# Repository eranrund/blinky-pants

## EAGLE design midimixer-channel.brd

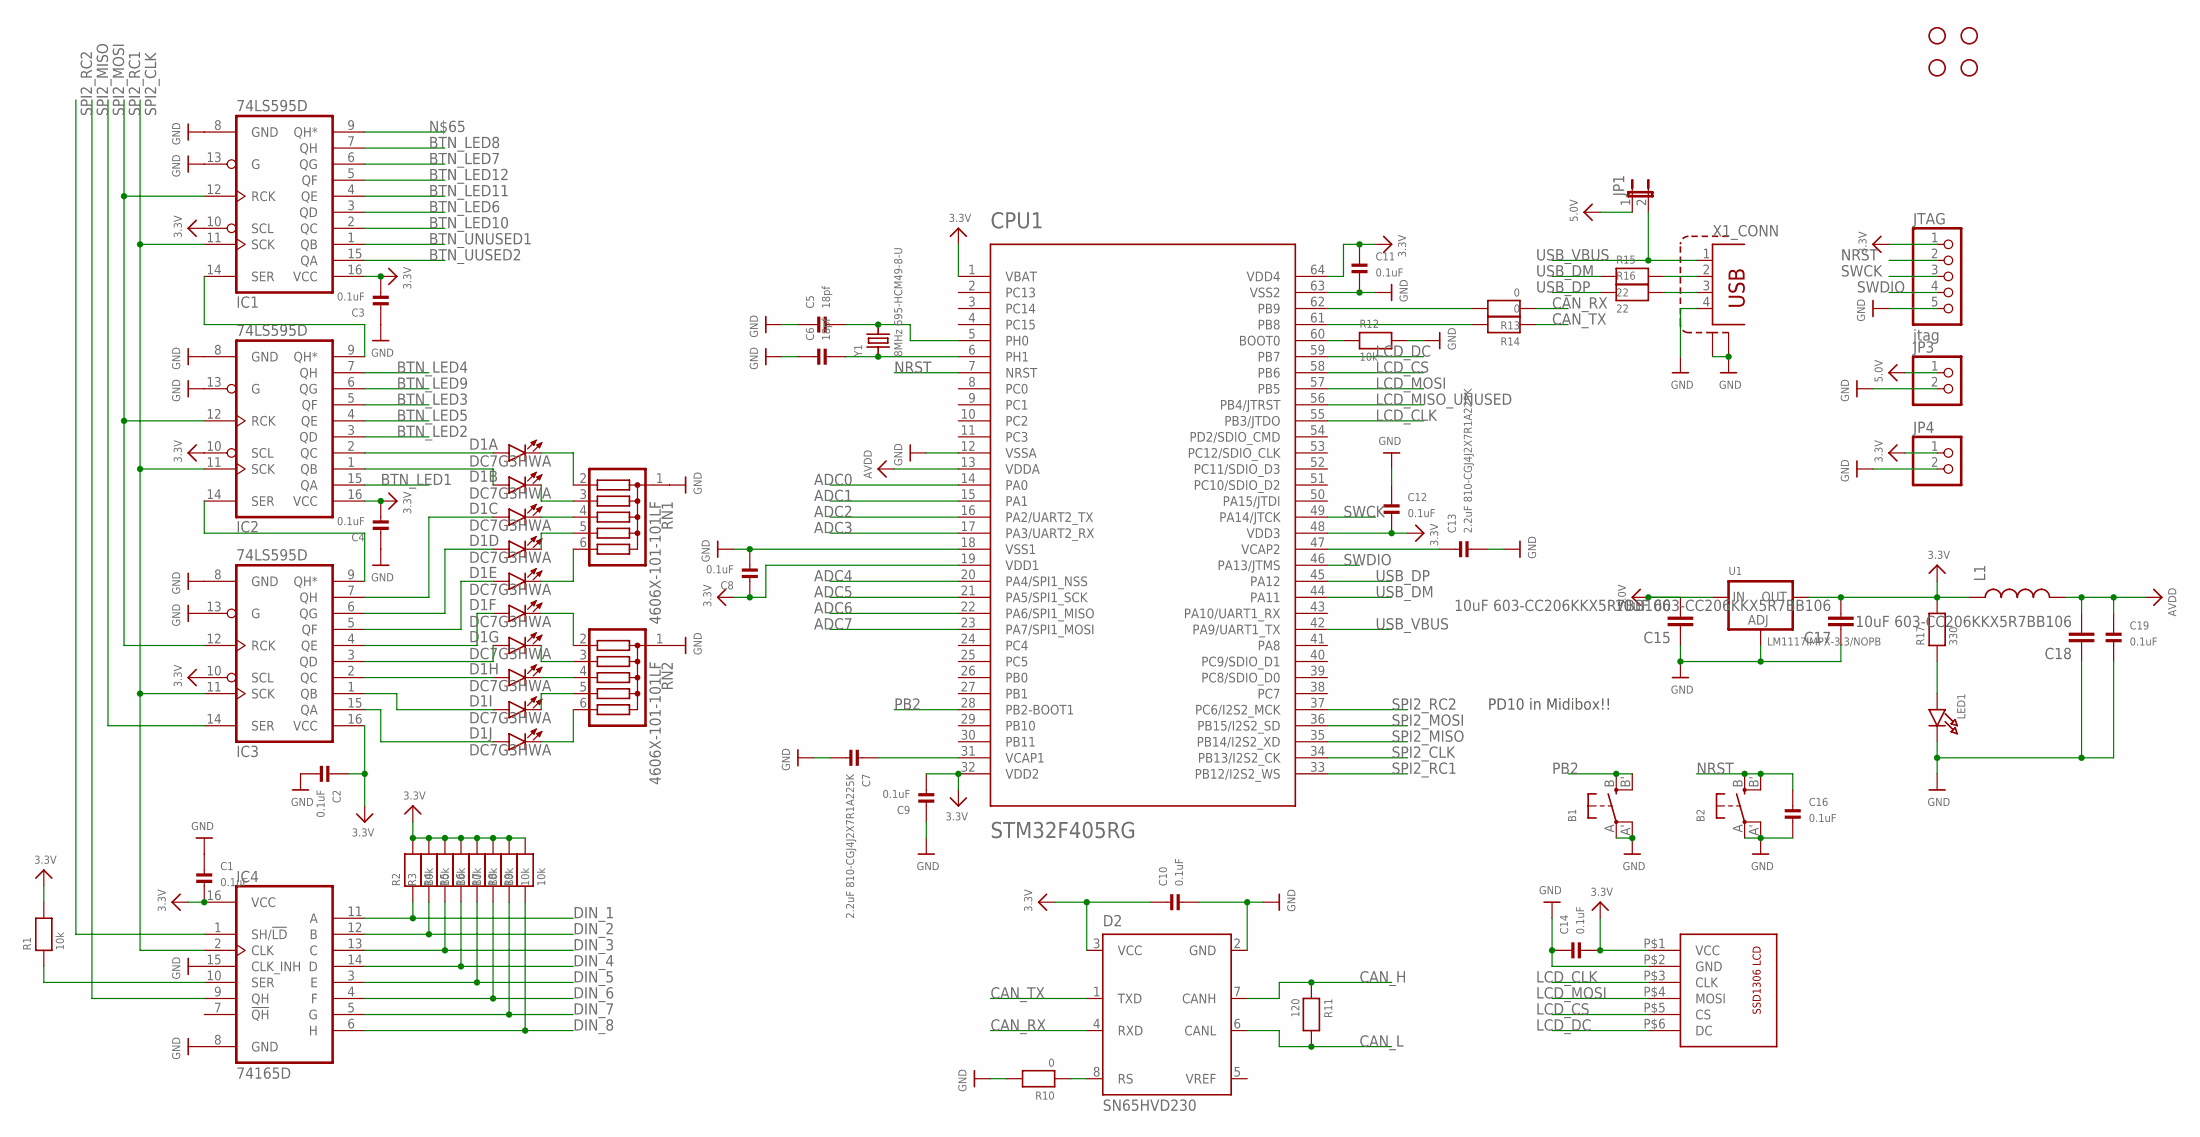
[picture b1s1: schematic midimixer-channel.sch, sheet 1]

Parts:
B1, B2: SWITCH_TACT_SMT; EVQ-Q2
C1, C2, C3, C4, C8, C9, C10, C11, C12, C14, C16, C19: 0.1uF; 0603
C5, C6: 18pf; 0603
C7, C13: 2.2uF 810-CGJ4J2X7R1A225K; 0805
C15, C17, C18: 10uF 603-CC206KKX5R7BB106; 1206
CPU1: STM32F405RG; TQFP64
D1: DC7G3HWA; LED_BARGAPH_10
D2: SN65HVD230; SO8
H1, H2, H3, H4: STAND-OFF
IC1, IC2, IC3: 74LS595D; SO16
IC4: 74165D; SO16
JP1: JUMPER2
JP3, JP4: HEADER-1X2ROUND; 1X02_ROUND
JTAG: jtag; 1X05_ROUND_76
L1: INDUCTOR0805; 0805
LCD1: SSD1306-ALI
LED1: LED0603; CHIPLED_0603
R1, R2, R3, R4, R5, R6, R7, R8, R9, R12: 10k; _0603
R10, R13, R14: 0; _0603
R11: 120; _0603
R15, R16: 22; 0603
R17: 330; 0603
RN1, RN2: 4606X-101-101LF; SIL6
U1: LM1117IMPX-3.3/NOPB; SOT223-R
X1: TE-292304-1
Y1: 8MHz 695-HCM49-8-U; HC49UP

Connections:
3.3V: C1.2, C2.1, C3.2, C4.2, C8.1, C9.2, C10.1, C11.1, C12.2, C14.2, C17.2, CPU1.1 (VBAT), CPU1.19 (VDD1), CPU1.32 (VDD2), CPU1.48 (VDD3), CPU1.64 (VDD4), D2.3 (VCC), IC1.10 (SCL), IC1.16 (VCC), IC2.10 (SCL), IC2.16 (VCC), IC3.10 (SCL), IC3.16 (VCC), IC4.16 (VCC), JP4.1, JTAG.1, L1.1, LCD1.P$1 (VCC), R1.2, R2.2, R3.2, R4.2, R5.2, R6.2, R7.2, R8.2, R9.2, R17.2, U1.2 (OUT); also elsewhere on the board
5.0V: C15.2, JP1.1, JP3.1, U1.3 (IN)
ADC0: CPU1.14 (PA0); also elsewhere on the board
ADC1: CPU1.15 (PA1); also elsewhere on the board
ADC2: CPU1.16 (PA2/UART2_TX); also elsewhere on the board
ADC3: CPU1.17 (PA3/UART2_RX); also elsewhere on the board
ADC4: CPU1.20 (PA4/SPI1_NSS); also elsewhere on the board
ADC5: CPU1.21 (PA5/SPI1_SCK); also elsewhere on the board
ADC6: CPU1.22 (PA6/SPI1_MISO); also elsewhere on the board
ADC7: CPU1.23 (PA7/SPI1_MOSI); also elsewhere on the board
AVDD: C18.2, C19.1, CPU1.13 (VDDA), L1.2
BTN_LED1: IC2.15 (QA); also elsewhere on the board
BTN_LED2: IC2.3 (QD); also elsewhere on the board
BTN_LED3: IC2.5 (QF); also elsewhere on the board
BTN_LED4: IC2.7 (QH); also elsewhere on the board
BTN_LED5: IC2.4 (QE); also elsewhere on the board
BTN_LED6: IC1.3 (QD); also elsewhere on the board
BTN_LED7: IC1.6 (QG); also elsewhere on the board
BTN_LED8: IC1.7 (QH); also elsewhere on the board
BTN_LED9: IC2.6 (QG); also elsewhere on the board
BTN_LED10: IC1.2 (QC); also elsewhere on the board
BTN_LED11: IC1.4 (QE); also elsewhere on the board
BTN_LED12: IC1.5 (QF); also elsewhere on the board
BTN_UNUSED1: IC1.1 (QB)
BTN_UUSED2: IC1.15 (QA)
CAN_H: D2.7 (CANH), R11.1
CAN_L: D2.6 (CANL), R11.2
CAN_RX: D2.4 (RXD), R13.1
CAN_TX: D2.1 (TXD), R14.1
DIN_1: IC4.11 (A), R2.1; also elsewhere on the board
DIN_2: IC4.12 (B), R3.1; also elsewhere on the board
DIN_3: IC4.13 (C), R4.1; also elsewhere on the board
DIN_4: IC4.14 (D), R5.1
DIN_5: IC4.3 (E), R6.1; also elsewhere on the board
DIN_6: IC4.4 (F), R7.1; also elsewhere on the board
DIN_7: IC4.5 (G), R8.1; also elsewhere on the board
DIN_8: IC4.6 (H), R9.1
GND: B1.A, B1.A' (P1), B2.A, B2.A' (P1), C1.1, C2.2, C3.1, C4.1, C5.1, C6.1, C7.2, C8.2, C9.1, C10.2, C11.2, C12.1, C13.2, C14.1, C15.1, C16.2, C17.1, C18.1, C19.2, CPU1.12 (VSSA), CPU1.18 (VSS1), CPU1.63 (VSS2), D2.2 (GND), IC1.8 (GND), IC1.13 (G), IC2.8 (GND), IC2.13 (G), IC3.8 (GND), IC3.13 (G), IC4.8 (GND), IC4.15 (CLK_INH), JP3.2, JP4.2, JTAG.5, LCD1.P$2 (GND), LED1.C, R10.2, R12.2, RN1.1, RN2.1, U1.1 (ADJ), X1.4, X1.P$1 (S1), X1.P$2 (S2); also elsewhere on the board
LCD_CLK: CPU1.55 (PB3/JTDO), LCD1.P$3 (CLK)
LCD_CS: CPU1.58 (PB6), LCD1.P$5 (CS)
LCD_DC: CPU1.59 (PB7), LCD1.P$6 (DC)
LCD_MISO_UNUSED: CPU1.56 (PB4/JTRST)
LCD_MOSI: CPU1.57 (PB5), LCD1.P$4 (MOSI)
unnamed: C6.2, CPU1.6 (PH1), Y1.1
unnamed: C5.2, CPU1.5 (PH0), Y1.2
unnamed: C13.1, CPU1.47 (VCAP2)
unnamed: C7.1, CPU1.31 (VCAP1)
unnamed: LED1.A, R17.1
unnamed: CPU1.60 (BOOT0), R12.1
unnamed: R15.2, X1.2
unnamed: R16.2, X1.3
unnamed: D1.2 (A), IC2.1 (QB)
unnamed: IC1.14 (SER), IC2.9 (QH*)
unnamed: CPU1.62 (PB9), R13.2
unnamed: D1.20 (C), RN1.2
unnamed: D1.19 (C), RN1.3
unnamed: D1.18 (C), RN1.4
unnamed: D1.17 (C), RN1.5
unnamed: D1.16 (C), RN1.6
unnamed: D1.15 (C), RN2.2
unnamed: D1.14 (C), RN2.3
unnamed: D1.13 (C), RN2.4
unnamed: D1.12 (C), RN2.5
unnamed: D1.11 (C), RN2.6
unnamed: CPU1.61 (PB8), R14.2
unnamed: IC4.10 (SER), R1.1
unnamed: D1.1 (A), IC2.2 (QC)
unnamed: D1.10 (A), IC3.15 (QA)
unnamed: D1.9 (A), IC3.1 (QB)
unnamed: D1.8 (A), IC3.2 (QC)
unnamed: D1.7 (A), IC3.3 (QD)
unnamed: D1.6 (A), IC3.4 (QE)
unnamed: D1.5 (A), IC3.5 (QF)
unnamed: D1.4 (A), IC3.6 (QG)
unnamed: D1.3 (A), IC3.7 (QH)
unnamed: IC2.14 (SER), IC3.9 (QH*)
unnamed: D2.8 (RS), R10.1
NRST: B2.B (S), B2.B' (S1), C16.1, CPU1.7 (NRST), JTAG.2
PB2: B1.B (S), B1.B' (S1), CPU1.28 (PB2-BOOT1)
SPI2_CLK: CPU1.34 (PB13/I2S2_CK), IC1.11 (SCK), IC2.11 (SCK), IC3.11 (SCK), IC4.2 (CLK)
SPI2_MISO: CPU1.35 (PB14/I2S2_XD), IC4.9 (QH)
SPI2_MOSI: CPU1.36 (PB15/I2S2_SD), IC3.14 (SER)
SPI2_RC1: CPU1.33 (PB12/I2S2_WS), IC1.12 (RCK), IC2.12 (RCK), IC3.12 (RCK)
SPI2_RC2: CPU1.37 (PC6/I2S2_MCK), IC4.1 (SH/!LD)
SWCK: CPU1.49 (PA14/JTCK), JTAG.3
SWDIO: CPU1.46 (PA13/JTMS), JTAG.4
USB_DM: CPU1.44 (PA11), R15.1
USB_DP: CPU1.45 (PA12), R16.1
USB_VBUS: CPU1.42 (PA9/UART1_TX), JP1.2, X1.1

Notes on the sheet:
PD10 in Midibox!!

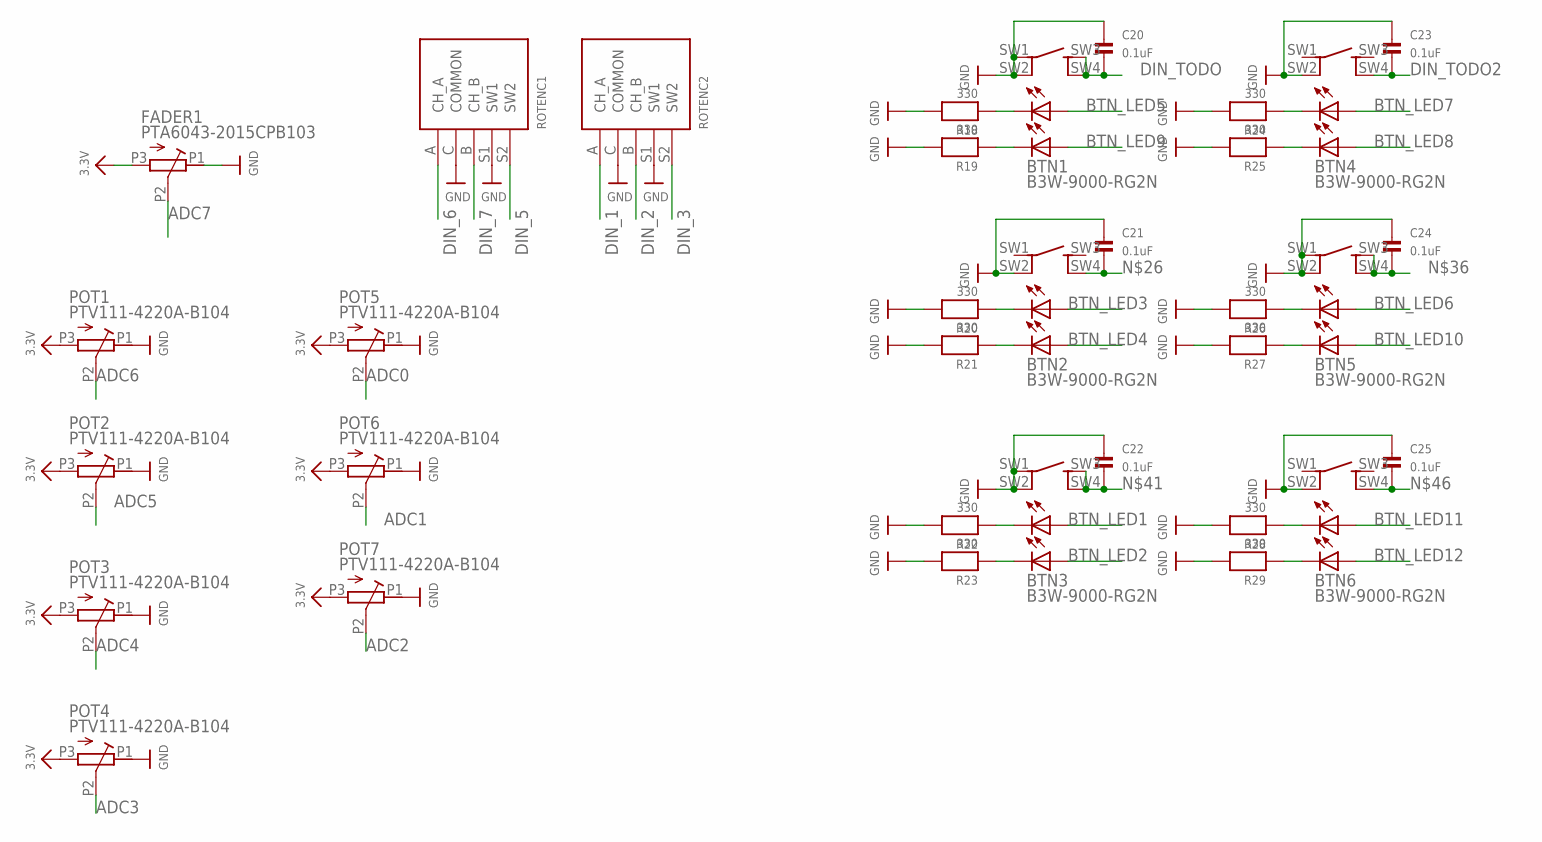
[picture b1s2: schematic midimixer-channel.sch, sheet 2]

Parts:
BTN1, BTN2, BTN3, BTN4, BTN5, BTN6: B3W-9000-RG2N; B3W-9000-X2X
C20, C21, C22, C23, C24, C25: 0.1uF; 0603
FADER1: PTA6043-2015CPB103
POT1, POT2, POT3, POT4, POT5, POT6, POT7: PTV111-4220A-B104; PTV111-4
R18, R19, R20, R21, R22, R23, R24, R25, R26, R27, R28, R29: 330; 0603
ROTENC1, ROTENC2: PEC11-4215K-S0024; PEC111-4XXXK-SXXXX

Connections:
3.3V: FADER1.P3 (E), POT1.P3 (E), POT2.P3 (E), POT3.P3 (E), POT4.P3 (E), POT5.P3 (E), POT6.P3 (E), POT7.P3 (E); also elsewhere on the board
ADC0: POT5.P2 (S); also elsewhere on the board
ADC1: POT6.P2 (S); also elsewhere on the board
ADC2: POT7.P2 (S); also elsewhere on the board
ADC3: POT4.P2 (S); also elsewhere on the board
ADC4: POT3.P2 (S); also elsewhere on the board
ADC5: POT2.P2 (S); also elsewhere on the board
ADC6: POT1.P2 (S); also elsewhere on the board
ADC7: FADER1.P2 (S); also elsewhere on the board
BTN_LED1: BTN3.LED1+; also elsewhere on the board
BTN_LED2: BTN3.LED2+; also elsewhere on the board
BTN_LED3: BTN2.LED1+; also elsewhere on the board
BTN_LED4: BTN2.LED2+; also elsewhere on the board
BTN_LED5: BTN1.LED1+; also elsewhere on the board
BTN_LED6: BTN5.LED1+; also elsewhere on the board
BTN_LED7: BTN4.LED1+; also elsewhere on the board
BTN_LED8: BTN4.LED2+; also elsewhere on the board
BTN_LED9: BTN1.LED2+; also elsewhere on the board
BTN_LED10: BTN5.LED2+; also elsewhere on the board
BTN_LED11: BTN6.LED1+; also elsewhere on the board
BTN_LED12: BTN6.LED2+; also elsewhere on the board
DIN_1: ROTENC2.A (CH_A); also elsewhere on the board
DIN_2: ROTENC2.B (CH_B); also elsewhere on the board
DIN_3: ROTENC2.S2 (SW2); also elsewhere on the board
DIN_5: ROTENC1.S2 (SW2); also elsewhere on the board
DIN_6: ROTENC1.A (CH_A); also elsewhere on the board
DIN_7: ROTENC1.B (CH_B); also elsewhere on the board
DIN_TODO: BTN1.SW3 (SW2_A), BTN1.SW4 (SW2_B), C20.2
DIN_TODO2: BTN4.SW4 (SW2_B), C23.2
GND: BTN1.SW1 (SW1_A), BTN1.SW2 (SW1_B), BTN2.SW2 (SW1_B), BTN3.SW1 (SW1_A), BTN3.SW2 (SW1_B), BTN4.SW2 (SW1_B), BTN5.SW1 (SW1_A), BTN5.SW2 (SW1_B), BTN6.SW2 (SW1_B), C20.1, C21.1, C22.1, C23.1, C24.1, C25.1, FADER1.P1 (A), POT1.P1 (A), POT2.P1 (A), POT3.P1 (A), POT4.P1 (A), POT5.P1 (A), POT6.P1 (A), POT7.P1 (A), R18.2, R19.2, R20.2, R21.2, R22.2, R23.2, R24.2, R25.2, R26.2, R27.2, R28.2, R29.2, ROTENC1.C (COMMON), ROTENC1.S1 (SW1), ROTENC2.C (COMMON), ROTENC2.S1 (SW1); also elsewhere on the board
unnamed: BTN1.LED1-, R18.1
unnamed: BTN1.LED2-, R19.1
unnamed: BTN2.LED1-, R20.1
unnamed: BTN2.LED2-, R21.1
unnamed: BTN2.SW4 (SW2_B), C21.2
unnamed: BTN4.LED1-, R24.1
unnamed: BTN4.LED2-, R25.1
unnamed: BTN5.LED1-, R26.1
unnamed: BTN5.LED2-, R27.1
unnamed: BTN5.SW3 (SW2_A), BTN5.SW4 (SW2_B), C24.2
unnamed: BTN3.LED1-, R22.1
unnamed: BTN3.LED2-, R23.1
unnamed: BTN3.SW3 (SW2_A), BTN3.SW4 (SW2_B), C22.2
unnamed: BTN6.LED1-, R28.1
unnamed: BTN6.LED2-, R29.1
unnamed: BTN6.SW4 (SW2_B), C25.2

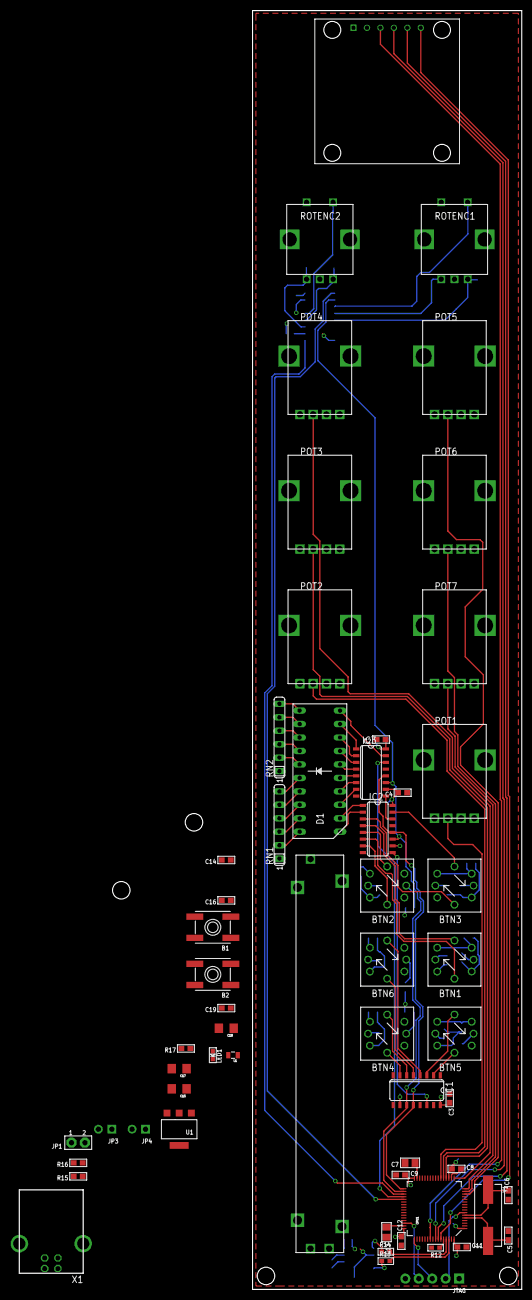
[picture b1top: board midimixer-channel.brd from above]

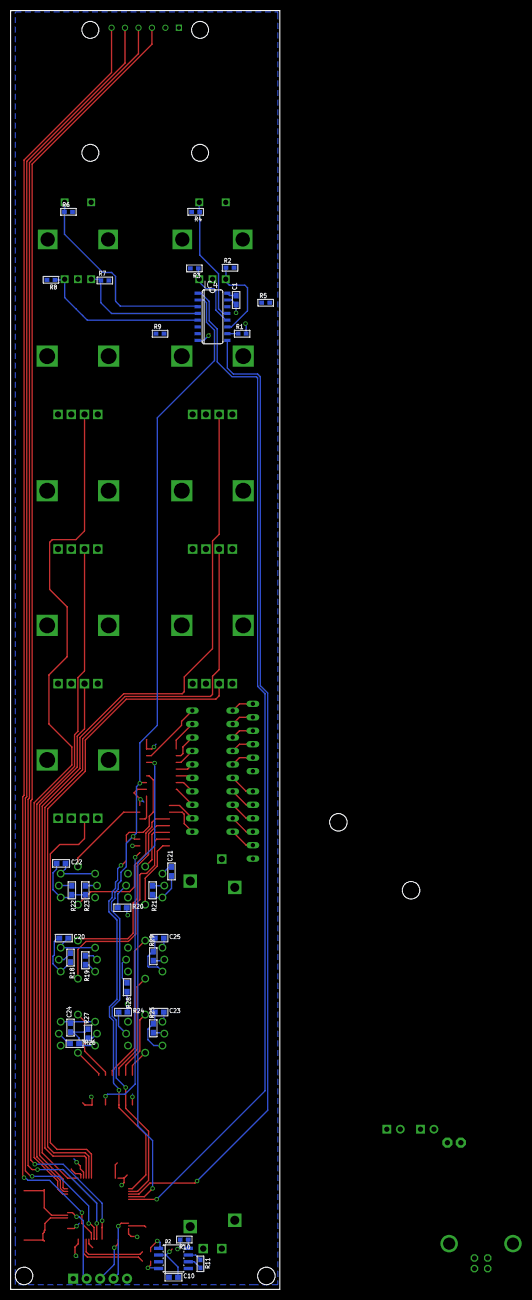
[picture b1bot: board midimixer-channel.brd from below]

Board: 2 copper layers, 50.8 x 241.3 mm, 95 parts (33 on the bottom side), 104 nets.

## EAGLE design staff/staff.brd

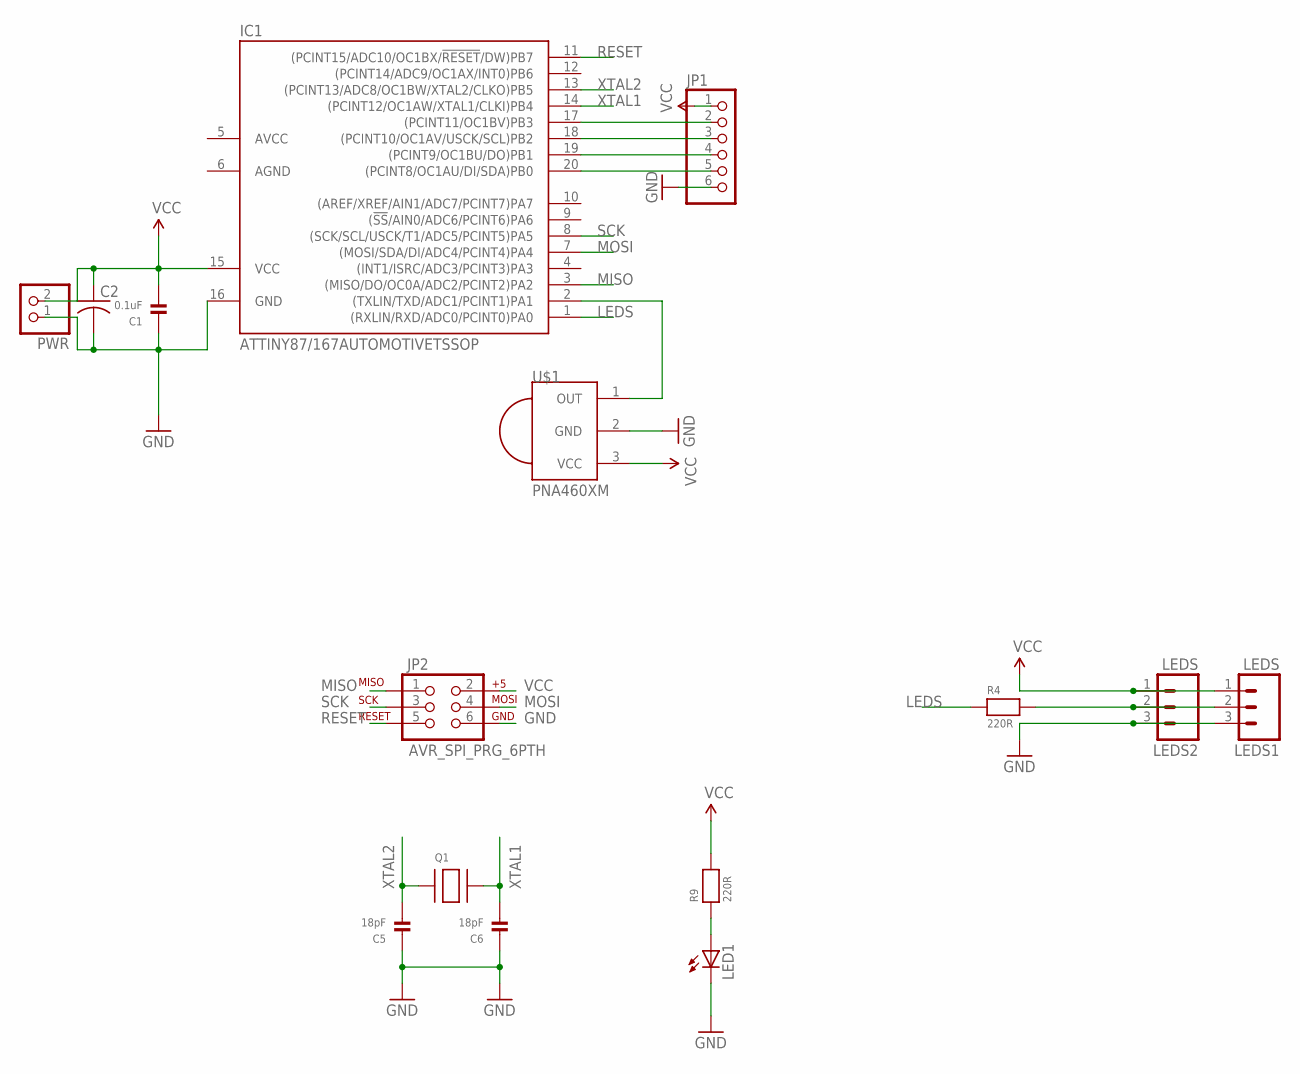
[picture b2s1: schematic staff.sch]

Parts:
C1: 0.1uF; 0603
C2: C-US025-025X050; C025-025X050
C5, C6: 18pF; 0603
IC1: ATTINY87/167AUTOMOTIVETSSOP; TSSOP20
JP1: PINHD-1X6CLEAN; 1X06-CLEAN
JP2: AVR_SPI_PRG_6PTH; 2X3
LED1: LEDCHIPLED_0603; CHIPLED_0603
LEDS1, LEDS2: LEDS; 1X03
PWR: PINHD-1X2; 1X02
Q1: CRYSTAL; ABLS7M2
R4, R9: 220R; 0603
U$1: PNA460XM

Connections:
GND: C1.1, C2.2, C5.1, C6.1, IC1.16 (GND), JP1.6, JP2.6, LED1.C, LEDS1.3, LEDS2.3, PWR.1, U$1.2 (GND)
LEDS: IC1.1 ((RXLIN/RXD/ADC0/PCINT0)PA0), R4.1
MISO: IC1.3 ((MISO/DO/OC0A/ADC2/PCINT2)PA2), JP2.1
MOSI: IC1.7 ((MOSI/SDA/DI/ADC4/PCINT4)PA4), JP2.4
unnamed: IC1.2 ((TXLIN/TXD/ADC1/PCINT1)PA1), U$1.1 (OUT)
unnamed: IC1.17 ((PCINT11/OC1BV)PB3), JP1.2
unnamed: IC1.18 ((PCINT10/OC1AV/USCK/SCL)PB2), JP1.3
unnamed: IC1.19 ((PCINT9/OC1BU/DO)PB1), JP1.4
unnamed: LED1.A, R9.1
unnamed: IC1.20 ((PCINT8/OC1AU/DI/SDA)PB0), JP1.5
unnamed: LEDS1.2, LEDS2.2, R4.2
RESET: IC1.11 ((PCINT15/ADC10/OC1BX/!RESET!/DW)PB7), JP2.5
SCK: IC1.8 ((SCK/SCL/USCK/T1/ADC5/PCINT5)PA5), JP2.3
VCC: C1.2, C2.1, IC1.15 (VCC), JP1.1, JP2.2, LEDS1.1, LEDS2.1, PWR.2, R9.2, U$1.3 (VCC)
XTAL1: C6.2, IC1.14 ((PCINT12/OC1AW/XTAL1/CLKI)PB4), Q1.P$2
XTAL2: C5.2, IC1.13 ((PCINT13/ADC8/OC1BW/XTAL2/CLKO)PB5), Q1.P$1

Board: 2 copper layers, 15 parts (2 on the bottom side), 16 nets, no tracks yet.

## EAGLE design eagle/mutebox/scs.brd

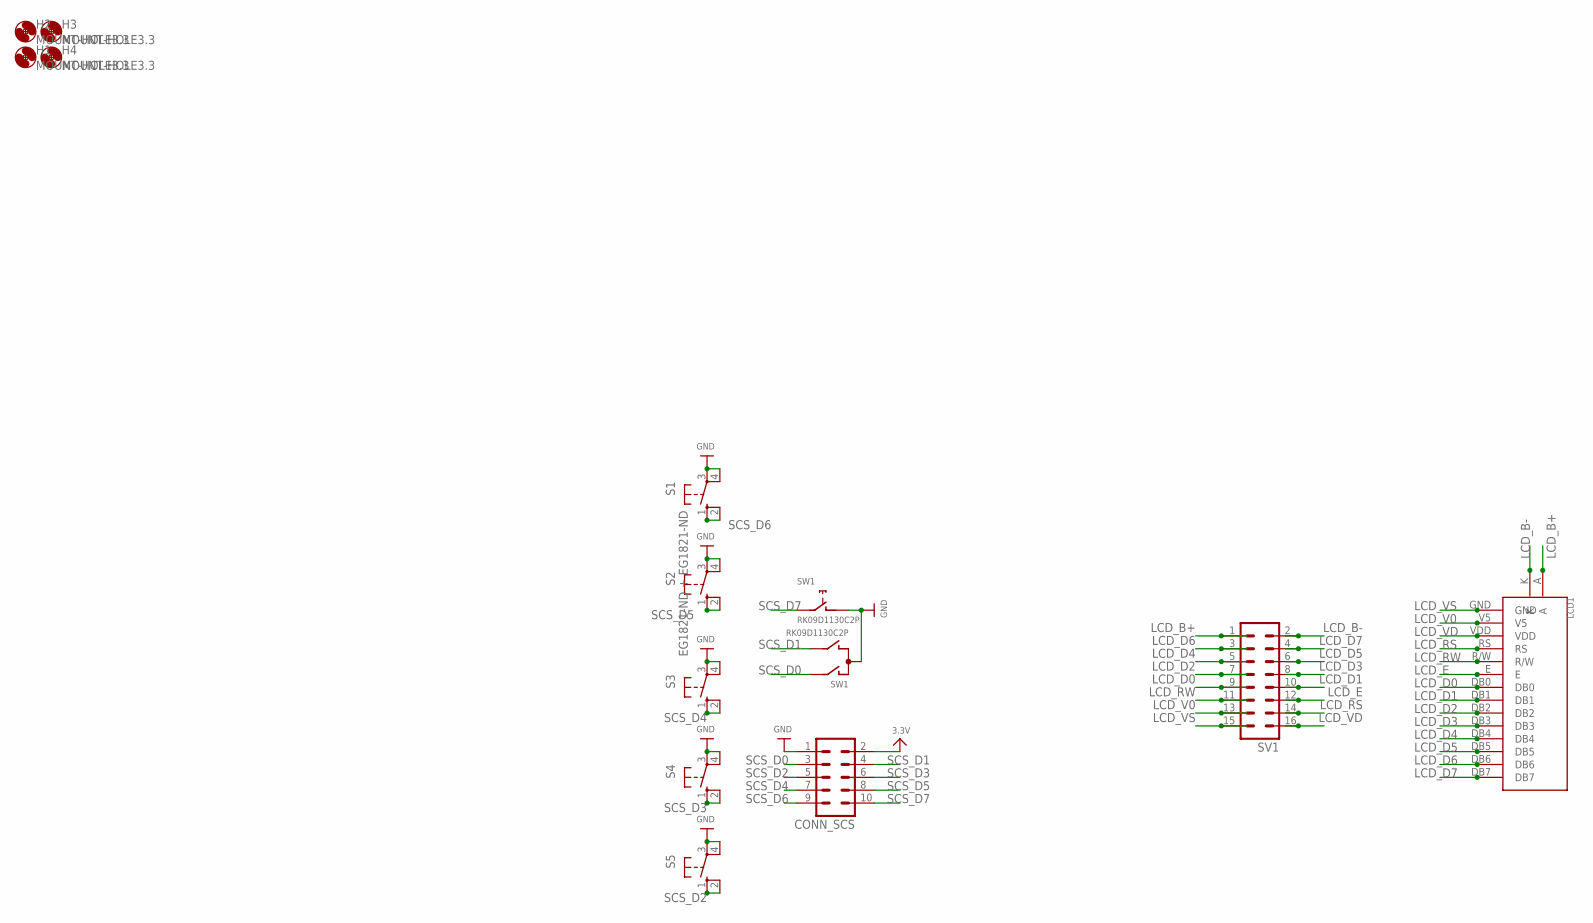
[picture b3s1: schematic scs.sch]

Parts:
CONN_SCS: ML10
H1, H2, H3, H4: MOUNT-HOLE3.3; 3,3
LCD1: NHD-C0220AA-FSW-FTW
S1: EG1821-ND + EG1821-ND; B3F-40XX
S2, S3, S4, S5: 40-XX; B3F-40XX
SV1: ML16
SW1: RK09D1130C2P; ALPS_EC12E_SW

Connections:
3.3V: CONN_SCS.2
GND: CONN_SCS.1, S1.3, S1.4 (P1), S2.3, S2.4 (P1), S3.3, S3.4 (P1), S4.3, S4.4 (P1), S5.3, S5.4 (P1), SW1.C, SW1.D (1)
LCD_B+: LCD1.A, SV1.1
LCD_B-: LCD1.K, SV1.2
LCD_D0: LCD1.DB0, SV1.9
LCD_D1: LCD1.DB1, SV1.10
LCD_D2: LCD1.DB2, SV1.7
LCD_D3: LCD1.DB3, SV1.8
LCD_D4: LCD1.DB4, SV1.5
LCD_D5: LCD1.DB5, SV1.6
LCD_D6: LCD1.DB6, SV1.3
LCD_D7: LCD1.DB7, SV1.4
LCD_E: LCD1.E, SV1.12
LCD_RS: LCD1.RS, SV1.14
LCD_RW: LCD1.R/W, SV1.11
LCD_V0: LCD1.V5, SV1.13
LCD_VD: LCD1.VDD, SV1.16
LCD_VS: LCD1.GND, SV1.15
SCS_D0: CONN_SCS.3, SW1.A
SCS_D1: CONN_SCS.4, SW1.B
SCS_D2: CONN_SCS.5, S5.1 (S), S5.2 (S1)
SCS_D3: CONN_SCS.6, S4.1 (S), S4.2 (S1)
SCS_D4: CONN_SCS.7, S3.1 (S), S3.2 (S1)
SCS_D5: CONN_SCS.8, S2.1 (S), S2.2 (S1)
SCS_D6: CONN_SCS.9, S1.1 (S), S1.2 (S1)
SCS_D7: CONN_SCS.10, SW1.E (2)

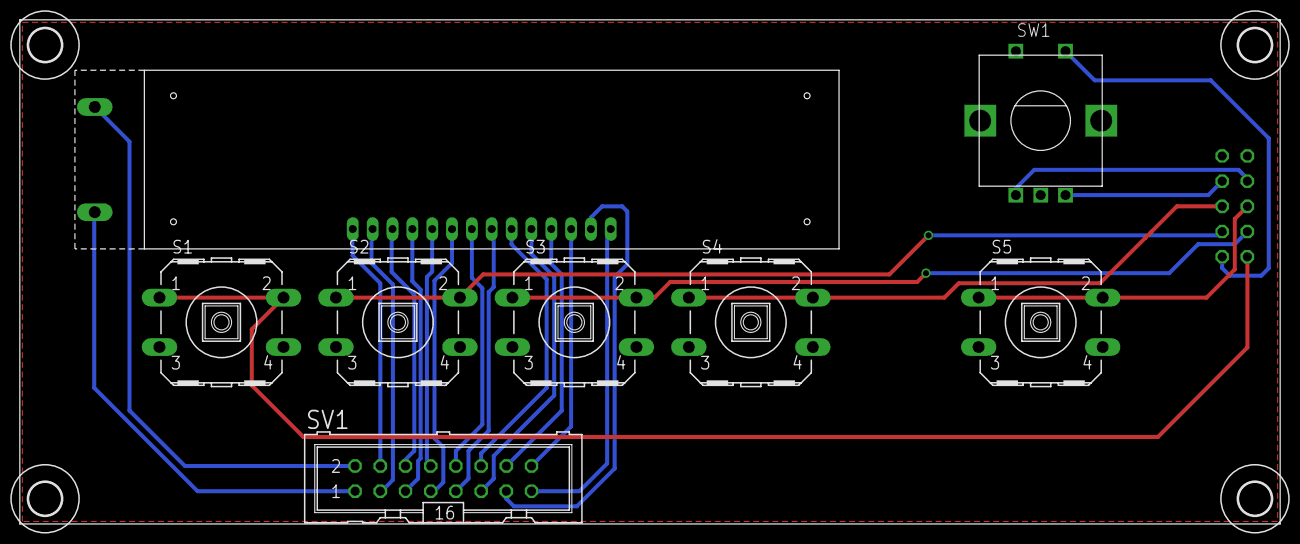
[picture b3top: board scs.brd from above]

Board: 2 copper layers, 127.0 x 50.8 mm, 13 parts (1 on the bottom side), 25 nets.

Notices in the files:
parts and their libraries:
SparkFun-Electromechanical: Licensing: CC v3.0 Share-Alike You are welcome to use this library for commercial purposes.
microbuilder: This work is placed in the public domain, and may be freely used for commercial and non-commercial work with the following conditions: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
